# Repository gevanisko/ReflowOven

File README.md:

# Reflow Oven

A custom toaster-oven-based solder reflow oven designed for assembling surface-mount PCB projects. This repository contains the hardware design files, KiCad PCB project, and STM32 firmware source code for a microcontroller-controlled reflow oven.

## Overview

This project converts a standard toaster oven into a controlled solder reflow oven. The goal is to create a repeatable heating system that can follow a solder reflow temperature profile for assembling surface-mount components.

The system is built around a custom PCB and an STM32 microcontroller. The controller reads temperature feedback, drives the oven heating element through a relay/control circuit, and provides user control for starting and monitoring the reflow process.

This project was inspired by the DIY reflow oven concept shown in the Instructables project: [DIY REFLOW OVEN](https://www.instructables.com/DIY-REFLOW-OVEN/). That project demonstrates the general idea of modifying a toaster oven into a solder reflow oven, while this repository focuses on my own STM32-based hardware and PCB implementation.

## Features

- Custom PCB designed in KiCad
- STM32-based embedded controller
- Toaster oven heating control
- Temperature feedback for reflow profile control
- Hardware files for schematic and PCB layout
- STM32CubeIDE project files
- Firmware source code written primarily in C
- Designed to support surface-mount PCB assembly

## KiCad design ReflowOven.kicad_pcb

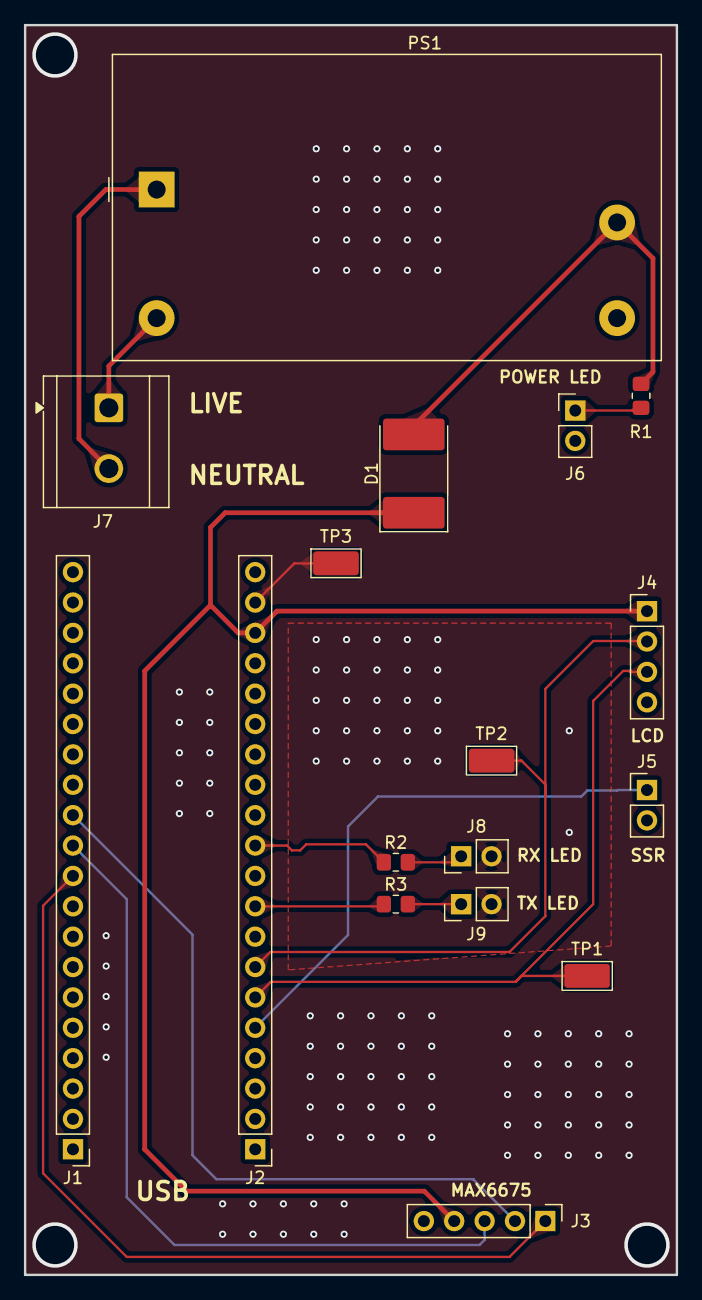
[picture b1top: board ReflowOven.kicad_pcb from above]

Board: 2 copper layers, 54.5 x 104.5 mm, 17 parts (0 on the bottom side), 16 nets.

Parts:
D1: D_Schottky; D_3220_8050Metric_Pad2.65x5.15mm_HandSolder
J1, J2: Conn_01x20_MountingPin; PinHeader_1x20_P2.54mm_Vertical
J3: Conn_01x05; PinHeader_1x05_P2.54mm_Vertical
J4: Conn_01x04; PinHeader_1x04_P2.54mm_Vertical
J5, J6, J8, J9: Conn_01x02; PinHeader_1x02_P2.54mm_Vertical
J7: Screw_Terminal_01x02; TerminalBlock_CUI_TB007-508-02_1x02_P5.08mm_Horizontal
PS1: IRM-05-5; Converter_ACDC_MeanWell_IRM-05-xx_THT
R1: 600; R_0805_2012Metric_Pad1.20x1.40mm_HandSolder
R2, R3: 220; R_0805_2012Metric_Pad1.20x1.40mm_HandSolder
TP1: TX; TestPoint_Keystone_5019_Miniature
TP2: RX; TestPoint_Keystone_5019_Miniature
TP3: GND; TestPoint_Keystone_5019_Miniature

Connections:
+5V: D1.1 (K), J2.18, J3.4, J4.1
+5V_S: D1.2 (A), PS1.4 (+Vo), R1.1
CS: J1.12, J3.2
DO: J1.10, J3.1
GND: J1.1, J1.2, J2.19, J3.5, J4.4, J5.2, J6.2, J8.2, J9.2, PS1.3 (-Vo), TP3.1 (1_1)
NEUT: J7.2, PS1.1 (AC/N)
unnamed: J2.9, R3.1
unnamed: J2.11, R2.1
unnamed: J6.1, R1.2
unnamed: J8.1, R2.2
unnamed: J9.1, R3.2
RX3_3V: J2.7, J4.2, TP2.1 (1_1)
SCK: J1.11, J3.3
SSR3_3V: J2.5, J5.1
TX3_3V: J2.6, J4.3, TP1.1 (1_1)
VAC: J7.1, PS1.2 (AC/L)

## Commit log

2026-05-14 Initial Commit for Reflow from laptop Kicad
2026-05-14 test
2026-05-14 initial test v2
2026-05-14 deleted backups
2026-05-14 stmcubeide file added
2026-05-26 update
    for fixing 3d printing
2026-06-19 SPI Lines updates
